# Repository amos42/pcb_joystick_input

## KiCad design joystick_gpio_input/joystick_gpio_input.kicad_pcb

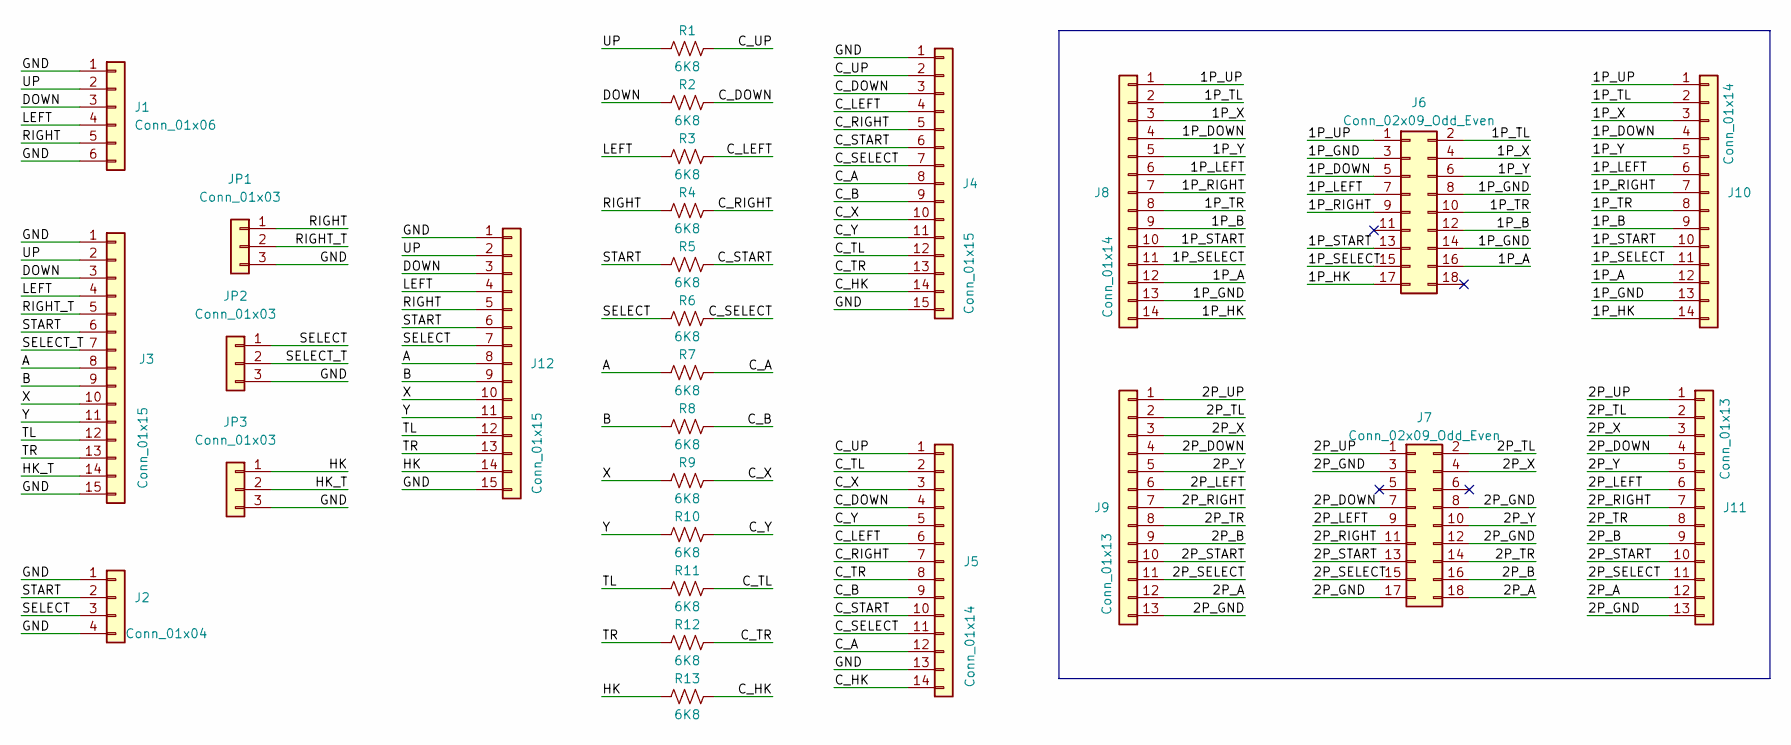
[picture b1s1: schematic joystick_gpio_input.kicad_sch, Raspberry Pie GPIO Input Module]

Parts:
J1: Conn_01x06; Molex_PicoBlade_53047-0610_1x06_P1.25mm_Vertical
J2: Conn_01x04; Molex_PicoBlade_53047-0410_1x04_P1.25mm_Vertical
J3: Conn_01x15; Molex_PicoBlade_53047-1510_1x15_P1.25mm_Vertical
J4, J12: Conn_01x15; PinHeader_1x15_P2.54mm_Vertical
J5, J10: Conn_01x14; conn_ex_1x14_P1.25mm_Vertical_Left_Labeled
J6, J7: Conn_02x09_Odd_Even; PinSocket_2x09_P2.54mm_Vertical
J8: Conn_01x14; conn_ex_1x14_P1.25mm_Vertical_Right_Labeled
J9: Conn_01x13; conn_ex_1x13_P1.25mm_Vertical_Right_Labeled
J11: Conn_01x13; conn_ex_1x13_P1.25mm_Vertical_Left_Labeled
JP1, JP2, JP3: Conn_01x03; PinHeader_1x03_P2.54mm_Vertical
R1, R2, R3, R4, R5, R6, R7, R8, R9, R10, R11, R12, R13: 6K8; R_0805_2012Metric_Pad1.20x1.40mm_HandSolder

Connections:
/1P_A: J6.16, J8.12, J10.12
/1P_B: J6.12, J8.9, J10.9
/1P_DOWN: J6.5, J8.4, J10.4
/1P_GND: J6.3, J6.8, J6.14, J8.13, J10.13
/1P_HK: J6.17, J8.14, J10.14
/1P_LEFT: J6.7, J8.6, J10.6
/1P_RIGHT: J6.9, J8.7, J10.7
/1P_SELECT: J6.15, J8.11, J10.11
/1P_START: J6.13, J8.10, J10.10
/1P_TL: J6.2, J8.2, J10.2
/1P_TR: J6.10, J8.8, J10.8
/1P_UP: J6.1, J8.1, J10.1
/1P_X: J6.4, J8.3, J10.3
/1P_Y: J6.6, J8.5, J10.5
/2P_A: J7.18, J9.12, J11.12
/2P_B: J7.16, J9.9, J11.9
/2P_DOWN: J7.7, J9.4, J11.4
/2P_GND: J7.3, J7.8, J7.12, J7.17, J9.13, J11.13
/2P_LEFT: J7.9, J9.6, J11.6
/2P_RIGHT: J7.11, J9.7, J11.7
/2P_SELECT: J7.15, J9.11, J11.11
/2P_START: J7.13, J9.10, J11.10
/2P_TL: J7.2, J9.2, J11.2
/2P_TR: J7.14, J9.8, J11.8
/2P_UP: J7.1, J9.1, J11.1
/2P_X: J7.4, J9.3, J11.3
/2P_Y: J7.10, J9.5, J11.5
/A: J3.8, J12.8, R7.1
/B: J3.9, J12.9, R8.1
/C_A: J4.8, J5.12, R7.2
/C_B: J4.9, J5.9, R8.2
/C_DOWN: J4.3, J5.4, R2.2
/C_HK: J4.14, J5.14, R13.2
/C_LEFT: J4.4, J5.6, R3.2
/C_RIGHT: J4.5, J5.7, R4.2
/C_SELECT: J4.7, J5.11, R6.2
/C_START: J4.6, J5.10, R5.2
/C_TL: J4.12, J5.2, R11.2
/C_TR: J4.13, J5.8, R12.2
/C_UP: J4.2, J5.1, R1.2
/C_X: J4.10, J5.3, R9.2
/C_Y: J4.11, J5.5, R10.2
/DOWN: J1.3, J3.3, J12.3, R2.1
/GND: J1.1, J1.6, J2.1, J2.4, J3.1, J3.15, J4.1, J4.15, J5.13, J12.1, J12.15, JP1.3, JP2.3, JP3.3
/HK: J12.14, JP3.1, R13.1
/HK_T: J3.14, JP3.2
/LEFT: J1.4, J3.4, J12.4, R3.1
/RIGHT: J1.5, J12.5, JP1.1, R4.1
/RIGHT_T: J3.5, JP1.2
/SELECT: J2.3, J12.7, JP2.1, R6.1
/SELECT_T: J3.7, JP2.2
/START: J2.2, J3.6, J12.6, R5.1
/TL: J3.12, J12.12, R11.1
/TR: J3.13, J12.13, R12.1
/UP: J1.2, J3.2, J12.2, R1.1
/X: J3.10, J12.10, R9.1
/Y: J3.11, J12.11, R10.1

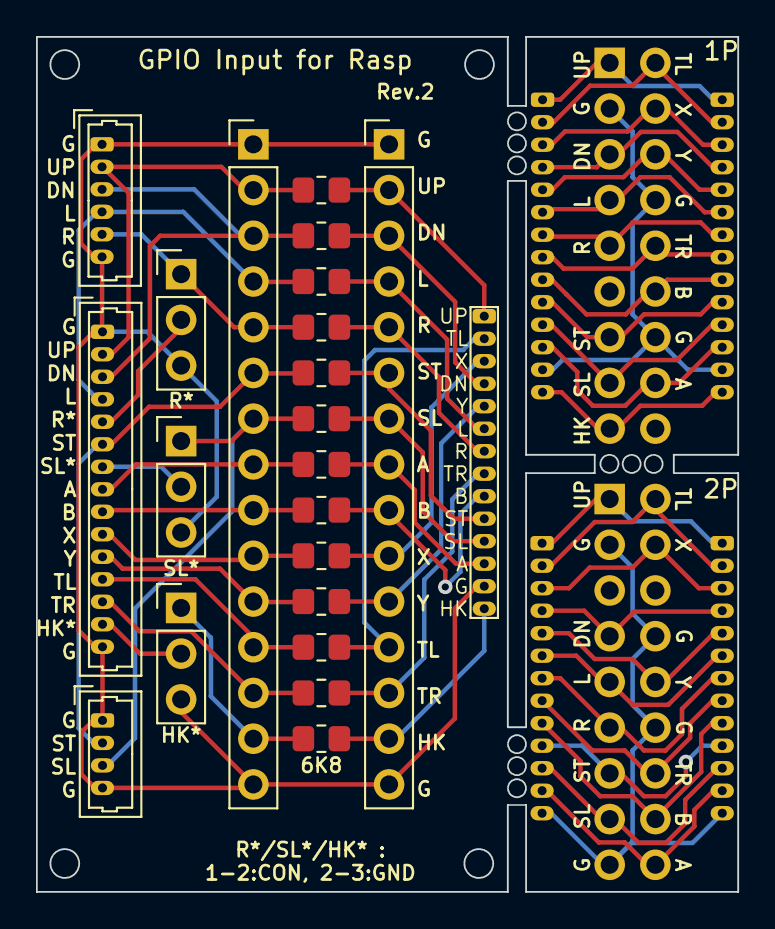
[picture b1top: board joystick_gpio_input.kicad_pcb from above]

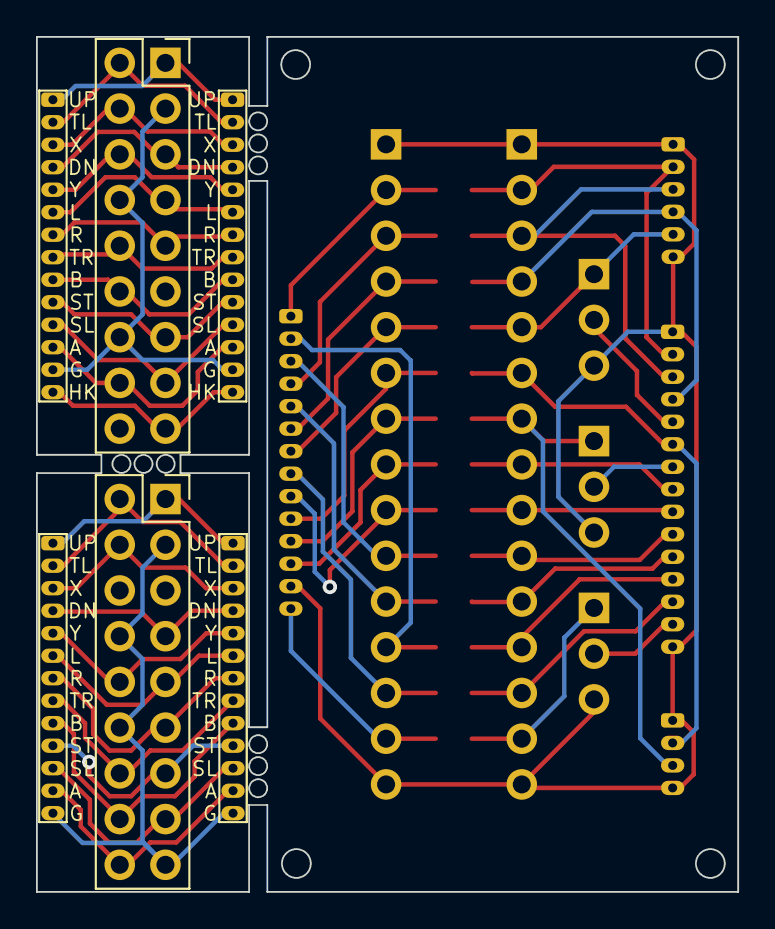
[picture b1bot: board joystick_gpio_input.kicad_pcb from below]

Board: 2 copper layers, 39.0 x 47.5 mm, 28 parts (6 on the bottom side), 57 nets.
